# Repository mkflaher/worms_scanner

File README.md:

# Microfluidic Device Image Processing

Kirina Gajadhar - Electrical Engineer

Cindy Tzapin - Electrical Engineer

Max Flynn - Electrical Engineer	

Meryl Flaherty - Computer Engineer

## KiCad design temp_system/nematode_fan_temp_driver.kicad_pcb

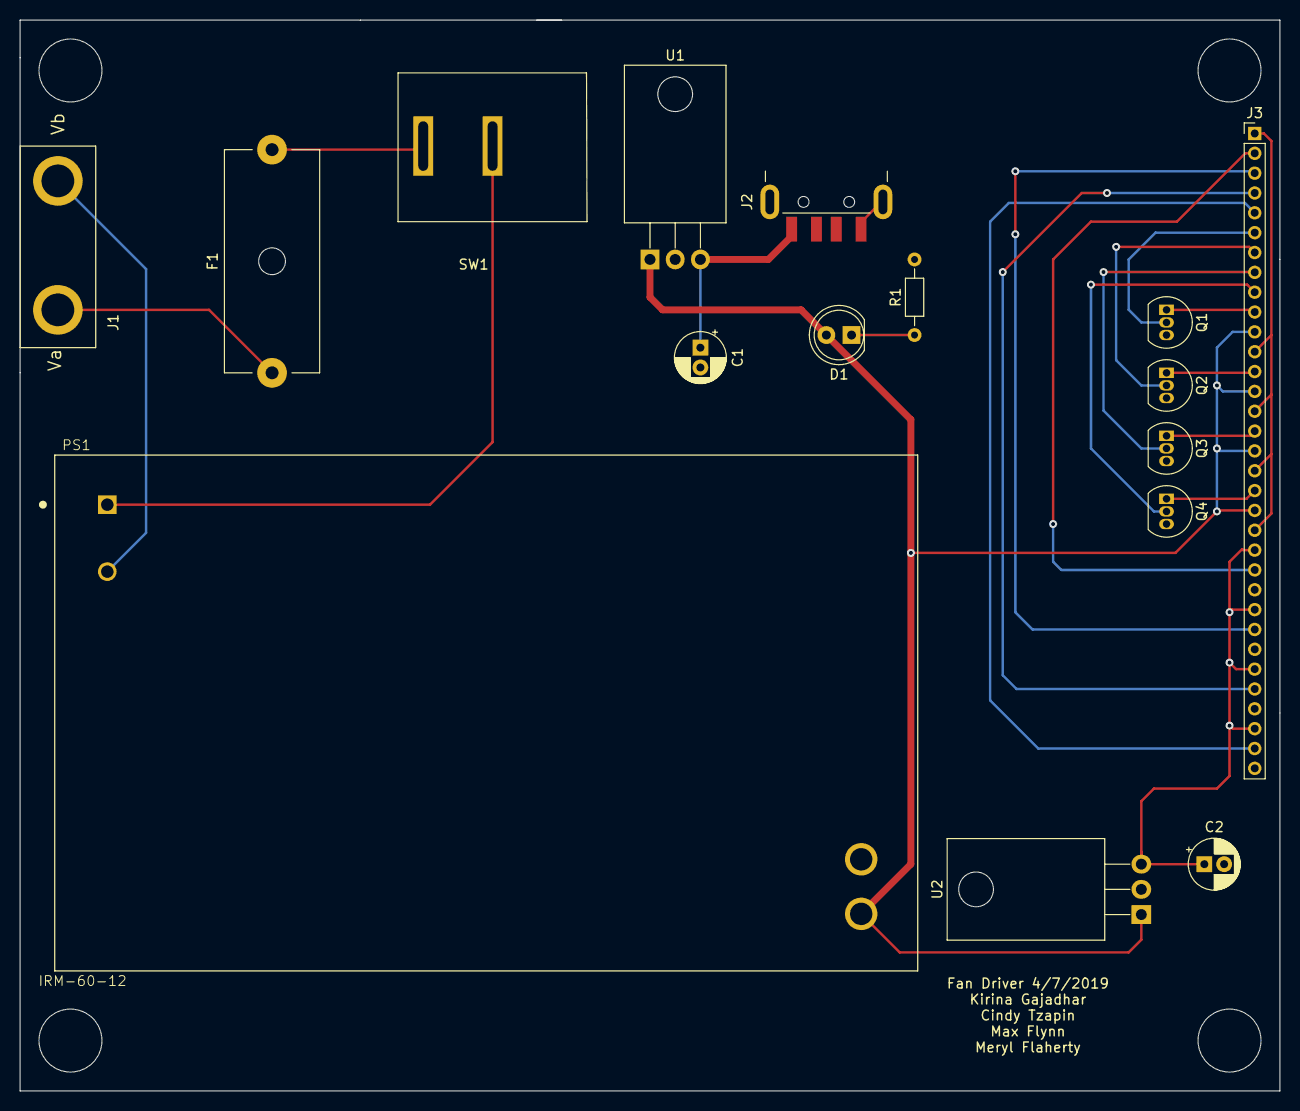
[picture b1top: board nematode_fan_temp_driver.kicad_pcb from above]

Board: 2 copper layers, 127.0 x 108.0 mm, 16 parts (0 on the bottom side), 22 nets.

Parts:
C1, C2: CP; CP_Radial_D5.0mm_P2.00mm
D1: LED; LED_D5.0mm
F1: 1A - 250V; Fuseholder_Cylinder-5x20mm_Schurter_0031_8201_Horizontal_Op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
J1: AC Socket IEC 320-C8; IEC_320_C8
J2: USB_A; USB_A_CNCTech_1001-011-01101_Horizontal
J3: Conn_01x33_Male; PinHeader_1x33_P2.00mm_Vertical
PS1: IRM-60-12; CONV_IRM-60-12
Q1, Q2, Q3, Q4: BS170; TO-92_Inline
R1: 1k; R_Axial_DIN0204_L3.6mm_D1.6mm_P7.62mm_Horizontal
SW1: SW_TOGGLE; toggle_switch
U1: 3A 5V Reg; TO-220-3_Horizontal_TabDown
U2: 1A 5V Reg; TO-220-3_Horizontal_TabDown

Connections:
5V: C2.1, J3.22, J3.25, J3.28, J3.31, U2.3
+12V: D1.2, J3.11, J3.14, J3.17, J3.20, PS1.+V, U1.1, U2.1
GND: C1.2, C2.2, J2.4, J2.5, J3.24, J3.27, J3.30, J3.33, PS1.V, Q1.3, Q2.3, Q3.3, Q4.3, R1.2, U1.2, U2.2
unnamed: C1.1, J2.1, U1.3
unnamed: D1.1, R1.1
unnamed: F1.1, J1.1
unnamed: F1.2, SW1.1
unnamed: J1.2, PS1.AC/N
unnamed: PS1.AC/L, SW1.2
fan_1_ctrl: J3.6, Q1.2
fan_1_src: J3.10, Q1.1
fan_2_ctrl: J3.7, Q2.2
fan_2_src: J3.13, Q2.1
fan_3_ctrl: J3.8, Q3.2
fan_3_src: J3.16, Q3.1
fan_4_ctrl: J3.9, Q4.2
fan_4_src: J3.19, Q4.1
fan_pwm: J3.1, J3.12, J3.15, J3.18, J3.21
temp_1: J3.2, J3.23
temp_2: J3.3, J3.26
temp_3: J3.4, J3.29
temp_4: J3.5, J3.32

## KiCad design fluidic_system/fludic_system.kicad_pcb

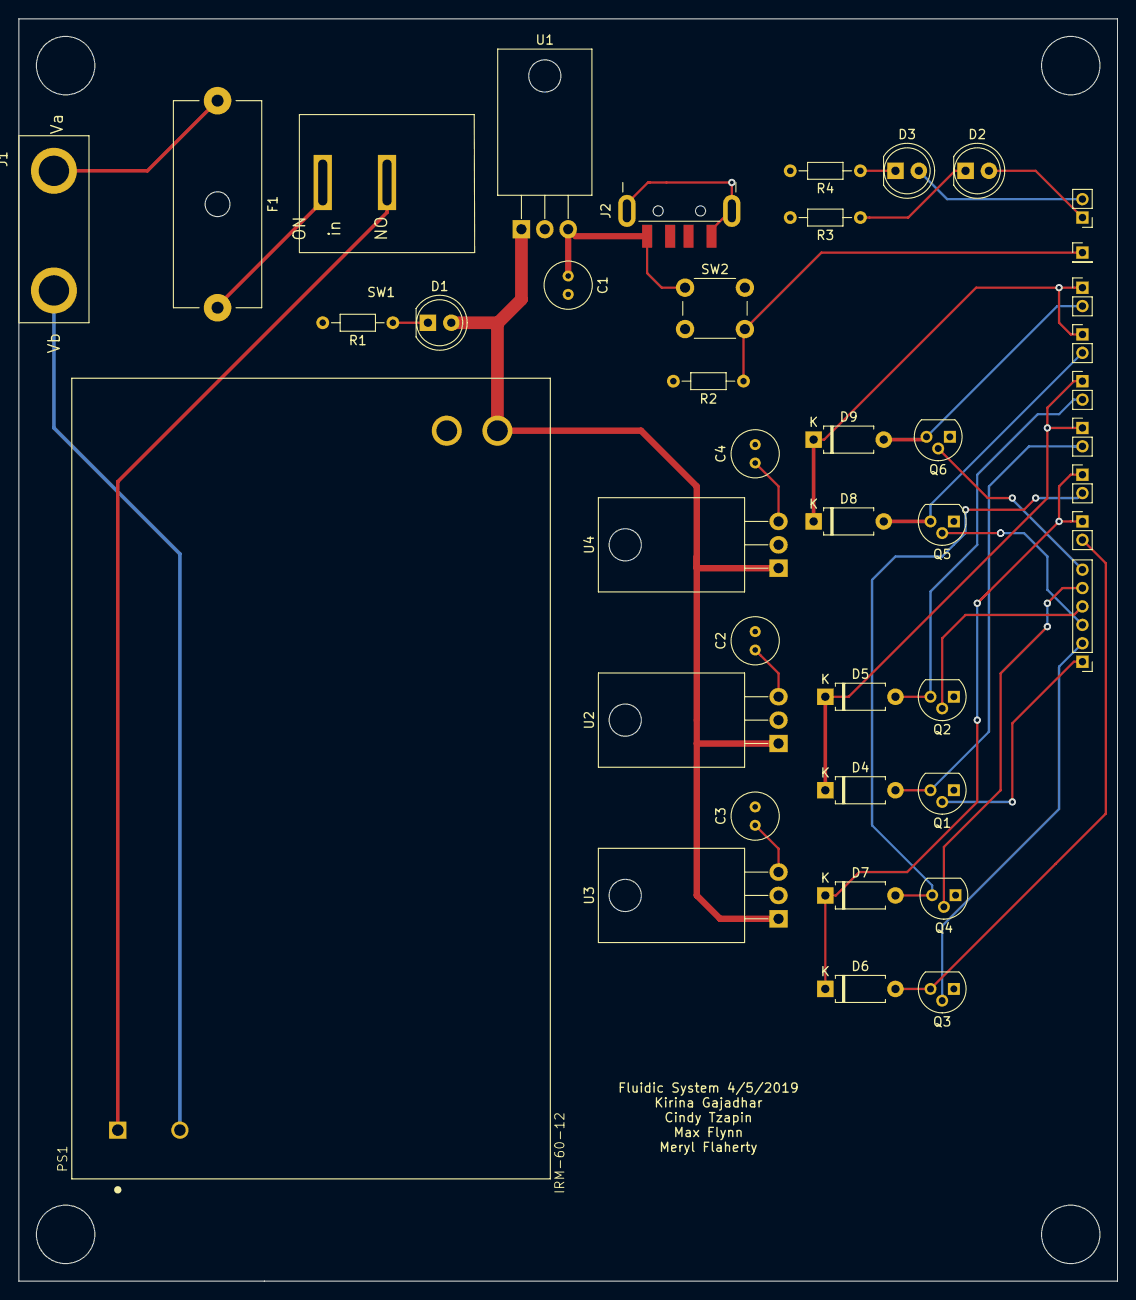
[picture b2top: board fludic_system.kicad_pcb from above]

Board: 2 copper layers, 119.4 x 137.2 mm, 42 parts (0 on the bottom side), 28 nets.

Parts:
C1, C2, C3, C4: 1u; C_Radial_D5.0mm_H5.0mm_P2.00mm
D1, D2, D3: LED; LED_D5.0mm
D4, D5, D6, D7, D8, D9: D; D_A-405_P7.62mm_Horizontal
F1: 1A - 250V; Fuseholder_Cylinder-5x20mm_Schurter_0031_8201_Horizontal_Op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
J1: AC Socket IEC 320-C8; IEC_320_C8
J2: USB_A; USB_A_CNCTech_1001-011-01101_Horizontal
J3: Conn_01x01_Male; PinHeader_1x01_P2.00mm_Vertical
J4: Conn_01x06_Male; PinHeader_1x06_P2.00mm_Vertical
J5, J6, J7, J8, J9, J10, J11: Conn_01x02_Male; PinHeader_1x02_P2.00mm_Vertical
PS1: IRM-60-12; CONV_IRM-60-12
Q1, Q2, Q3, Q4, Q5, Q6: 2N2222; TO-92
R1, R2, R3, R4: 1k; R_Axial_DIN0204_L3.6mm_D1.6mm_P7.62mm_Horizontal
SW1: SW_TOGGLE; toggle_switch
SW2: SW_Push; SW_PUSH_6mm
U1: 3A 5V Reg; TO-220-3_Horizontal_TabDown
U2, U3, U4: 1A 6V Reg; TO-220-3_Horizontal_TabDown

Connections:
+12V: D1.2, PS1.+V, U1.1, U2.1, U3.1, U4.1
GND: C1.2, C2.2, C3.2, C4.2, J2.4, J2.5, PS1.V, Q1.1, Q2.1, Q3.1, Q4.1, Q5.1, Q6.1, R1.2, R2.2, R3.2, R4.2, U1.2, U2.2, U3.2, U4.2
unnamed: C1.1, J2.1, SW2.1, U1.3
unnamed: C2.1, D4.1, D5.1, J6.1, J7.1, U2.3
unnamed: C3.1, D6.1, D7.1, J8.1, J9.1, U3.3
unnamed: C4.1, D8.1, D9.1, J10.1, J11.1, U4.3
unnamed: D1.1, R1.1
unnamed: D2.1, R3.1
unnamed: D3.1, R4.1
unnamed: D4.2, J6.2, Q1.3
unnamed: D5.2, J7.2, Q2.3
unnamed: D6.2, J8.2, Q3.3
unnamed: D7.2, J9.2, Q4.3
unnamed: D8.2, J10.2, Q5.3
unnamed: D9.2, J11.2, Q6.3
unnamed: F1.1, J1.1
unnamed: F1.2, SW1.1
unnamed: J1.2, PS1.AC/N
unnamed: PS1.AC/L, SW1.2
button: J3.1, R2.1, SW2.2
light_A: D2.2, J5.1
light_B: D3.2, J5.2
pump_1_ctrl: J4.1, Q1.2
pump_2_ctrl: J4.2, Q3.2
pump_3_ctrl: J4.3, Q5.2
pump_4_ctrl: J4.4, Q2.2
pump_5_ctrl: J4.5, Q4.2
pump_6_ctrl: J4.6, Q6.2

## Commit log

2019-05-09 readme, pcb files
2019-05-09 readme but for real
2019-05-09 fixed readme formatting
2019-05-09 scanner tray solidworks files
2019-05-09 temperature and fluidic system code
